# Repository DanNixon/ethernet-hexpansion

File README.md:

# Ethernet Hexpansion

W5500 based Ethernet and PoE hexpansion for the [Tildagon](https://tildagon.badge.emfcamp.org/) badge.

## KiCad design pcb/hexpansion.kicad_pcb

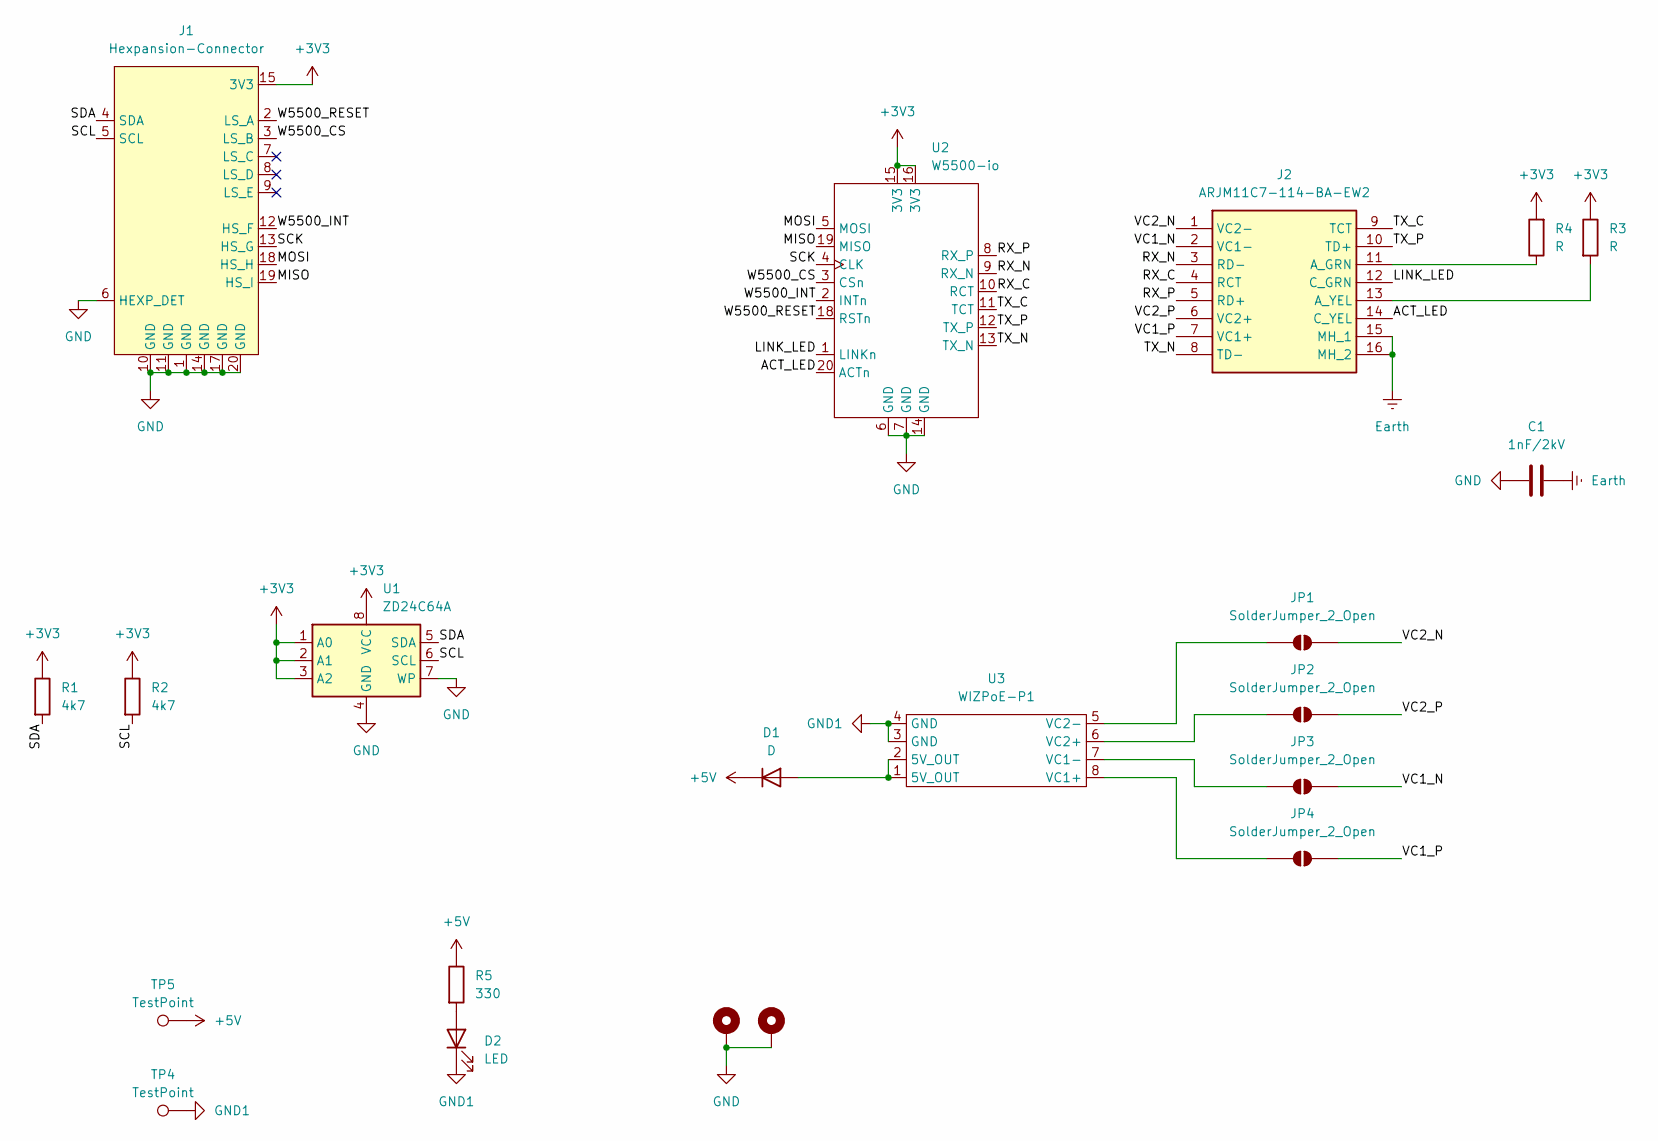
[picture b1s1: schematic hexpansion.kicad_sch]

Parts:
C1: 1nF/2kV; C_1206_3216Metric
D1: D; D_SOD-123
D2: LED; LED_1206_3216Metric
H1, H2: MountingHole_Pad; MountingHole_2.2mm_M2_Pad_Via
J1: Hexpansion-Connector; hexpansion-edge-connector
J2: ARJM11C7-114-BA-EW2; ARJM11C7114BAEW2; Mouser Part Number 815-RJM11C7114BAEW2
JP1, JP2, JP3, JP4: SolderJumper_2_Open; SolderJumper-2_P1.3mm_Open_RoundedPad1.0x1.5mm
R1, R2: 4k7; R_0805_2012Metric; LCSC C3017854
R3, R4: R; R_0805_2012Metric
R5: 330; R_0805_2012Metric
TP4: TestPoint; TestPoint_Pad_2.5x2.5mm
TP5: TestPoint; TestPoint_Pad_D2.5mm
U1: ZD24C64A; TSSOP-8_4.4x3mm_P0.65mm; LCSC C2875852
U2: W5500-io
U3: WIZPoE-P1

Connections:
+3V3: J1.15 (3V3), J1.16 (3V3), R1.1, R2.1, R3.1, R4.2, U1.1 (A0), U1.2 (A1), U1.3 (A2), U1.8 (VCC), U2.15 (3V3), U2.16 (3V3)
+5V: D1.1 (K), R5.1, TP5.1 (1_1)
/ACT_LED: J2.14 (C_YEL), U2.20 (ACTn)
/LINK_LED: J2.12 (C_GRN), U2.1 (LINKn)
/MISO: J1.19 (HS_I), U2.19 (MISO)
/MOSI: J1.18 (HS_H), U2.5 (MOSI)
/RX_C: J2.4 (RCT), U2.10 (RCT)
/RX_N: J2.3 (RD-), U2.9 (RX_N)
/RX_P: J2.5 (RD+), U2.8 (RX_P)
/SCK: J1.13 (HS_G), U2.4 (CLK)
/SCL: J1.5 (SCL), R2.2, U1.6 (SCL)
/SDA: J1.4 (SDA), R1.2, U1.5 (SDA)
/TX_C: J2.9 (TCT), U2.11 (TCT)
/TX_N: J2.8 (TD-), U2.13 (TX_N)
/TX_P: J2.10 (TD+), U2.12 (TX_P)
/VC1_N: J2.2 (VC1-), JP3.2 (B)
/VC1_P: J2.7 (VC1+), JP4.2 (B)
/VC2_N: J2.1 (VC2-), JP1.2 (B)
/VC2_P: J2.6 (VC2+), JP2.2 (B)
/W5500_CS: J1.3 (LS_B), U2.3 (CSn)
/W5500_INT: J1.12 (HS_F), U2.2 (INTn)
/W5500_RESET: J1.2 (LS_A), U2.18 (RSTn)
Earth: C1.1, J2.15 (MH_1), J2.16 (MH_2)
GND: C1.2, H1.1 (1_1), H2.1 (1_1), J1.1 (GND), J1.6 (HEXP_DET), J1.10 (GND), J1.11 (GND), J1.14 (GND), J1.17 (GND), J1.20 (GND), U1.4 (GND), U1.7 (WP), U2.6 (GND), U2.7 (GND), U2.14 (GND)
GND1: D2.1 (K), TP4.1 (1_1), U3.3 (GND), U3.4 (GND)
unnamed: D1.2 (A), U3.1 (5V_OUT), U3.2 (5V_OUT)
unnamed: D2.2 (A), R5.2
unnamed: J2.11 (A_GRN), R4.1
unnamed: J2.13 (A_YEL), R3.2
unnamed: JP1.1 (A), U3.5 (VC2-)
unnamed: JP2.1 (A), U3.6 (VC2+)
unnamed: JP3.1 (A), U3.7 (VC1-)
unnamed: JP4.1 (A), U3.8 (VC1+)

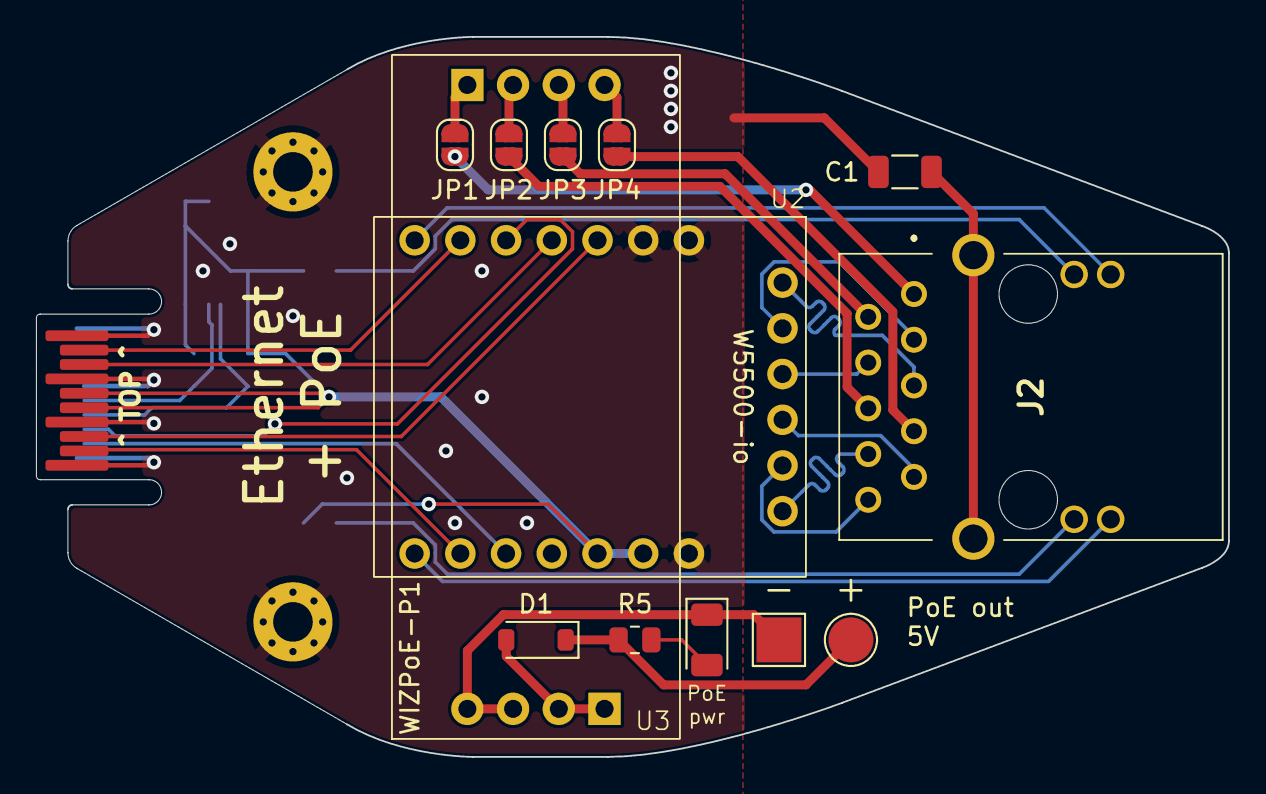
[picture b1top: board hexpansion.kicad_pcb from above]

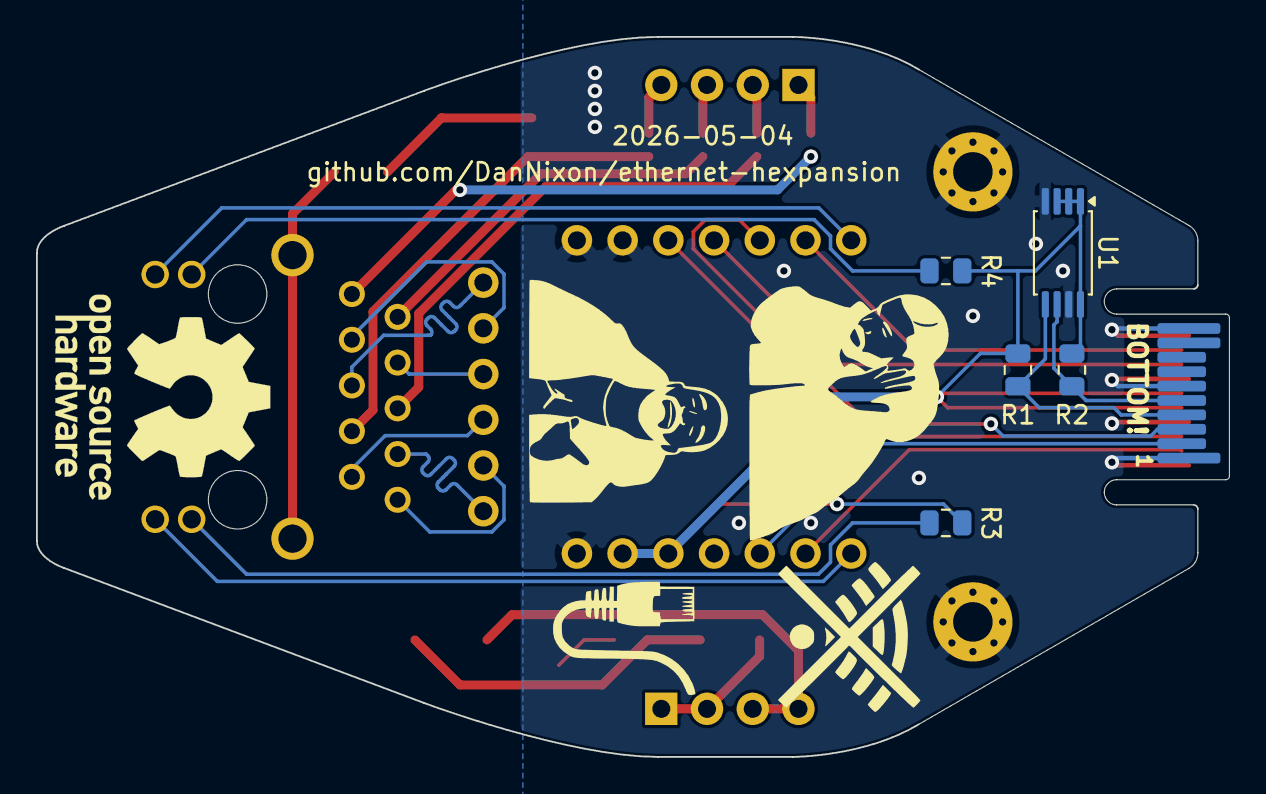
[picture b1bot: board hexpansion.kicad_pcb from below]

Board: 2 copper layers, 66.2 x 40.0 mm, 21 parts (5 on the bottom side), 33 nets.

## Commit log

2026-06-24 Add demo firmware
2026-06-24 Add demo firmware (#1)
